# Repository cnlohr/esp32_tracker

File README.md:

# esp32_tracker
ESP32 Tracker with the TS4231

THIS PROJECT IS NOT YET FUNCTIONAL.

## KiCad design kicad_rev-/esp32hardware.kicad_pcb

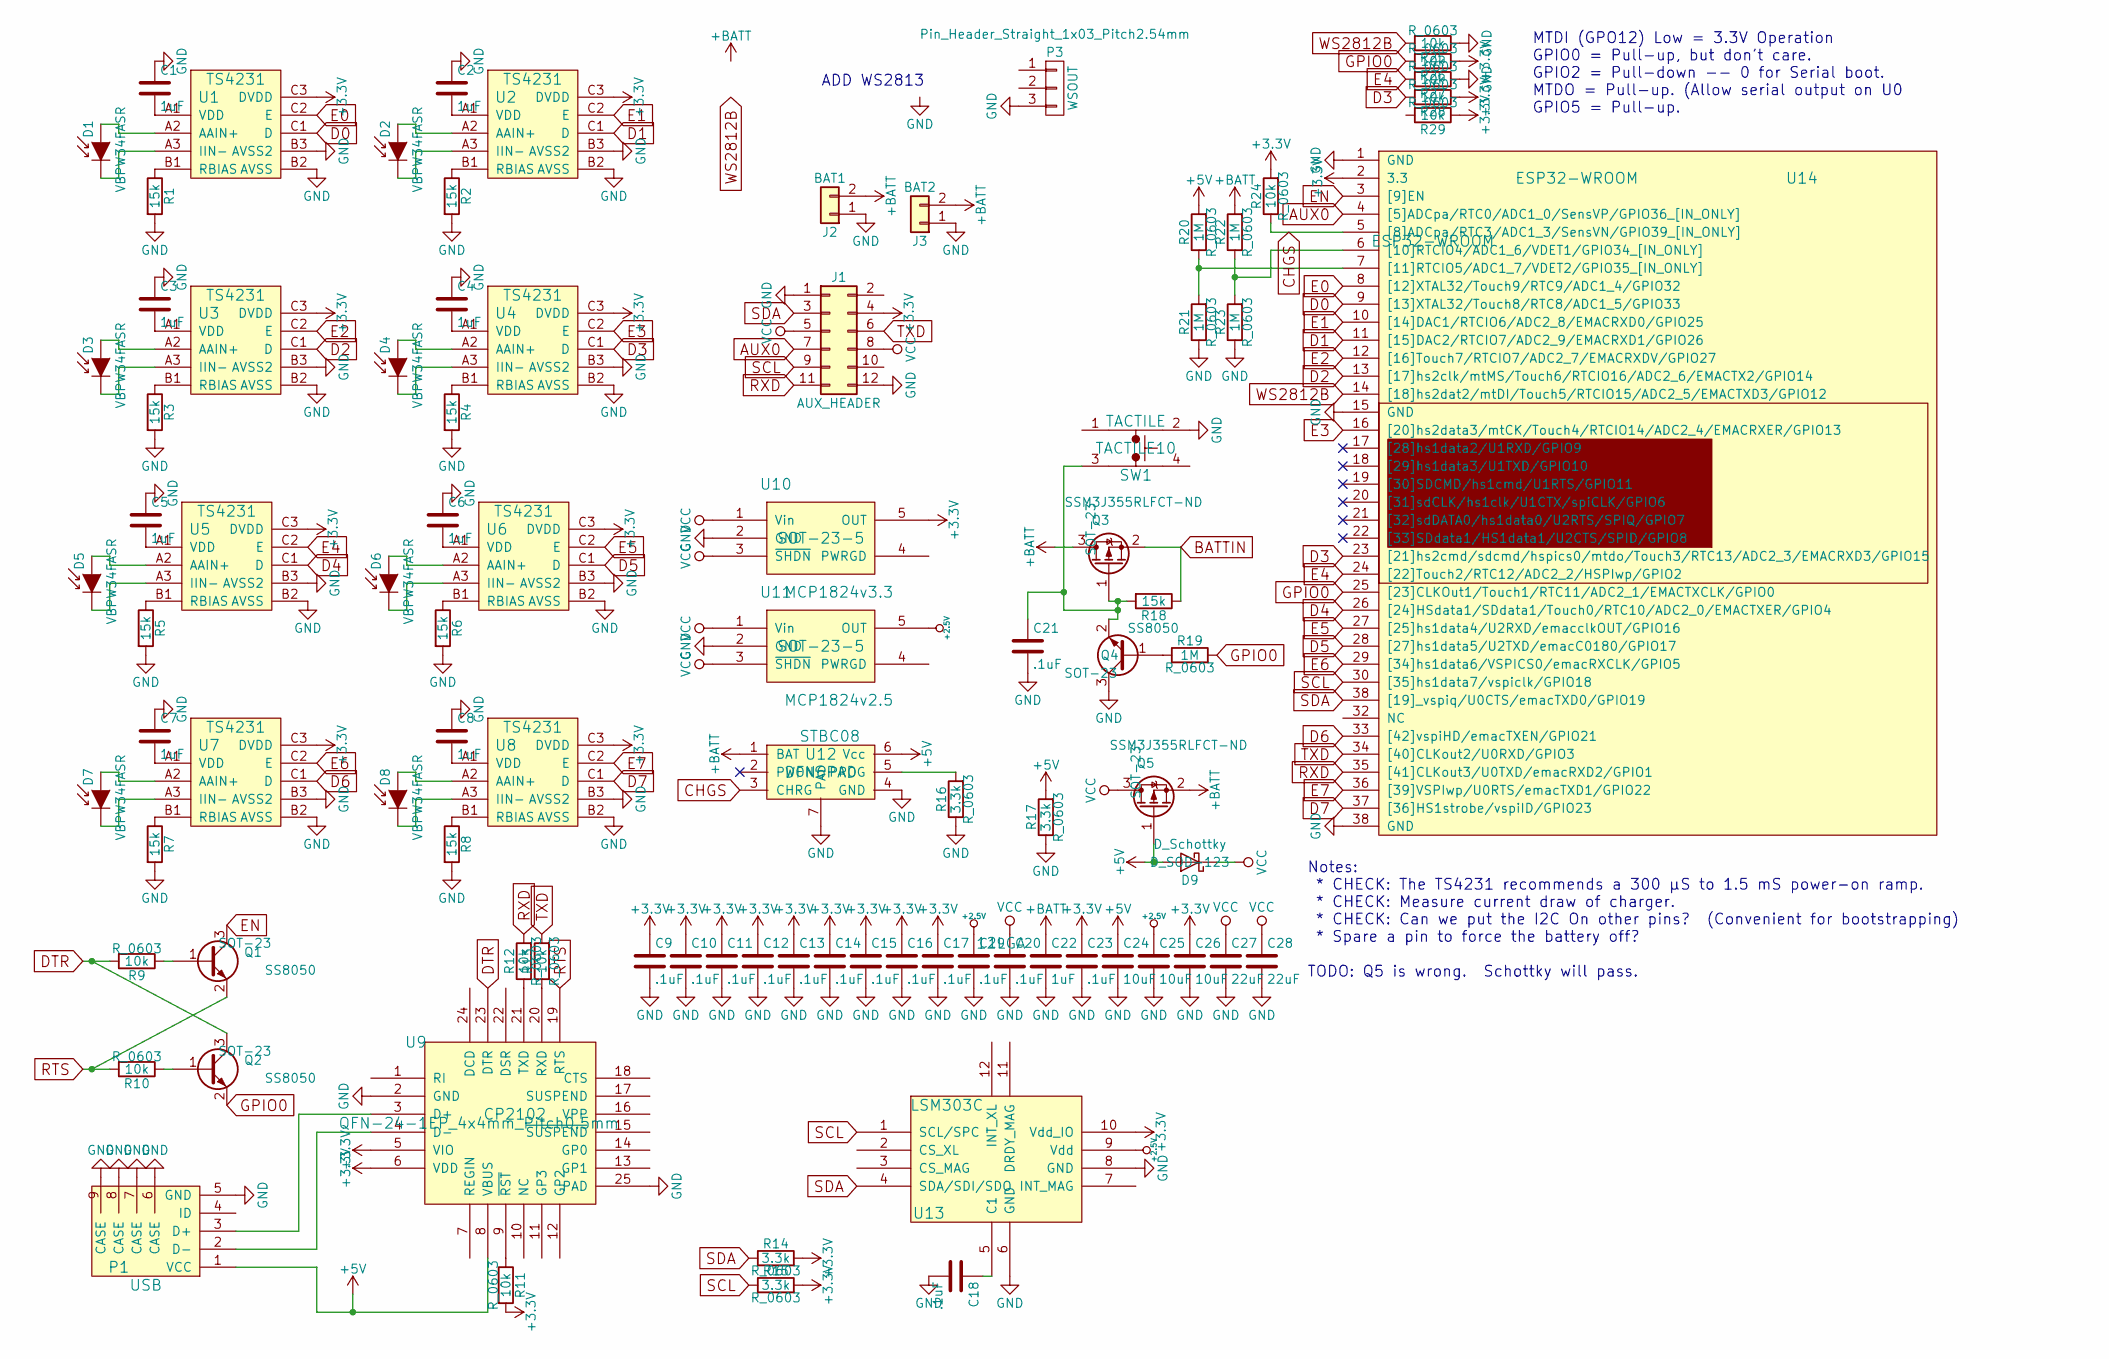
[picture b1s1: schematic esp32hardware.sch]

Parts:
C1, C2, C3, C4, C5, C6, C7, C8, C22: 1uF; C_0603
C9, C10, C11, C12, C13, C14, C15, C16, C17, C18, C19, C20, C21, C23: .1uF; C_0603
C24, C25, C26: 10uF; C_0603
C27, C28: 22uF; C_0603
D1, D2, D3, D4, D5, D6, D7, D8: VBPW34FASR
D9: D_Schottky; D_SOD-123
J1: AUX_HEADER; RIBBON12SMT
J2: BAT1; Pin_Header_Straight_1x02_Pitch2.54mm
J3: BAT2; Pin_Header_Straight_1x02_Pitch2.54mm
P1: USB; USBMicroB-10118194-0001LF
P3: WSOUT; Pin_Header_Straight_1x03_Pitch2.54mm
Q1, Q2, Q4: SS8050; SOT-23
Q3, Q5: SSM3J355RLFCT-ND; SOT-23
R1, R2, R3, R4, R5, R6, R7, R8, R18: 15k; R_0603
R9, R10, R11, R12, R13, R24, R25, R26, R27, R28, R29: 10k; R_0603
R14, R15, R16, R17: 3.3k; R_0603
R19, R20, R21, R22, R23: 1M; R_0603
SW1: TACTILE; TACTILE10
U1, U2, U3, U4, U5, U6, U7, U8: TS4231
U9: CP2102; QFN-24-1EP_4x4mm_Pitch0.5mm
U10: MCP1824v3.3; SOT-23-5
U11: MCP1824v2.5; SOT-23-5
U12: STBC08; DFN6PAD
U13: LSM303C; 12LGA
U14: ESP32-WROOM

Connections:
+2.5V: C19.1, C25.1, U11.5 (OUT), U13.9 (Vdd)
+3V3: C9.1, C10.1, C11.1, C12.1, C13.1, C14.1, C15.1, C16.1, C17.1, C23.1, C26.1, J1.4, R11.2, R14.2, R15.2, R24.2, R26.1, R28.1, R29.1, U1.C3 (DVDD), U2.C3 (DVDD), U3.C3 (DVDD), U4.C3 (DVDD), U5.C3 (DVDD), U6.C3 (DVDD), U7.C3 (DVDD), U8.C3 (DVDD), U9.5 (VIO), U9.6 (VDD), U10.5 (OUT), U13.10 (Vdd_IO), U14.2 (3.3)
+5V: C24.1, D9.2 (A), P1.1 (VCC), Q5.1 (G), R17.2, R20.2, U9.8 (VBUS), U12.6 (Vcc)
+BATT: C22.1, J2.2, J3.2, Q3.3 (D), Q5.2 (S), R22.2, U12.1 (BAT)
AUX0: J1.7, U14.4 ([5]ADCpa/RTC0/ADC1_0/SensVP/GPIO36_[IN_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)
BATTIN: Q3.2 (S), R18.1
CHGS: R24.1, U12.3 (CHRG), U14.5 ([8]ADCpa/RTC3/ADC1_3/SensVN/GPIO39_[IN_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)
D0: U1.C1 (D), U14.9 ([13]XTAL32/Touch8/RTC8/ADC1_5/GPIO33)
D1: U2.C1 (D), U14.11 ([15]DAC2/RTCIO7/ADC2_9/EMACRXD1/GPIO26)
D2: U3.C1 (D), U14.13 ([17]hs2clk/mtMS/Touch6/RTCIO16/ADC2_6/E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)
D3: R28.2, U4.C1 (D), U14.23 ([21]hs2cmd/sdcmd/hspics0/mtdo/Touch3/RT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)
D4: U5.C1 (D), U14.26 ([24]HSdata1/SDdata1/Touch0/RTC10/ADC2_0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)
D5: U6.C1 (D), U14.28 ([27]hs1data5/U2TXD/emacC0180/GPIO17)
D6: U7.C1 (D), U14.33 ([42]vspiHD/emacTXEN/GPIO21)
D7: U8.C1 (D), U14.37 ([36]HS1strobe/vspiID/GPIO23)
DTR: Q2.3 (C), R9.2, U9.23 (DTR)
E0: U1.C2 (E), U14.8 ([12]XTAL32/Touch9/RTC9/ADC1_4/GPIO32)
E1: U2.C2 (E), U14.10 ([14]DAC1/RTCIO6/ADC2_8/EMACRXD0/GPIO25)
E2: U3.C2 (E), U14.12 ([16]Touch7/RTCIO7/ADC2_7/EMACRXDV/GPIO27)
E3: U4.C2 (E), U14.16 ([20]hs2data3/mtCK/Touch4/RTCIO14/ADC2_4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)
E4: R27.2, U5.C2 (E), U14.24 ([22]Touch2/RTC12/ADC2_2/HSPIwp/GPIO2)
E5: U6.C2 (E), U14.27 ([25]hs1data4/U2RXD/emacclkOUT/GPIO16)
E6: U7.C2 (E), U14.29 ([34]hs1data6/VSPICS0/emacRXCLK/GPIO5)
E7: U8.C2 (E), U14.36 ([39]VSPIwp/U0RTS/emacTXD1/GPIO22)
EN: Q1.3 (C), U14.3 ([9]EN)
GPIO0: Q2.2 (E), R19.2, R26.2, U14.25 ([23]CLKOut1/Touch1/RTC11/ADC2_1/EMACTXC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)
unnamed: C1.2, U1.A1 (VDD)
unnamed: C2.2, U2.A1 (VDD)
unnamed: C3.2, U3.A1 (VDD)
unnamed: C4.2, U4.A1 (VDD)
unnamed: C5.2, U5.A1 (VDD)
unnamed: C6.2, U6.A1 (VDD)
unnamed: C7.2, U7.A1 (VDD)
unnamed: C8.2, U8.A1 (VDD)
unnamed: C18.1, U13.5 (C1)
unnamed: C21.1, Q3.1 (G), Q4.2 (E), R18.2, SW1.3
unnamed: D1.1 (K), U1.A3 (IIN-)
unnamed: D1.2 (A), U1.A2 (AAIN+)
unnamed: D2.1 (K), U2.A3 (IIN-)
unnamed: D2.2 (A), U2.A2 (AAIN+)
unnamed: D3.1 (K), U3.A3 (IIN-)
unnamed: D3.2 (A), U3.A2 (AAIN+)
unnamed: D4.1 (K), U4.A3 (IIN-)
unnamed: D4.2 (A), U4.A2 (AAIN+)
unnamed: D5.1 (K), U5.A3 (IIN-)
unnamed: D5.2 (A), U5.A2 (AAIN+)
unnamed: D6.1 (K), U6.A3 (IIN-)
unnamed: D6.2 (A), U6.A2 (AAIN+)
unnamed: D7.1 (K), U7.A3 (IIN-)
unnamed: D7.2 (A), U7.A2 (AAIN+)
unnamed: D8.1 (K), U8.A3 (IIN-)
unnamed: D8.2 (A), U8.A2 (AAIN+)
unnamed: P1.2 (D-), U9.4 (D-)
unnamed: P1.3 (D+), U9.3 (D+)
unnamed: Q1.1 (B), R9.1
unnamed: Q2.1 (B), R10.1
unnamed: Q4.1 (B), R19.1
unnamed: R1.1, U1.B1 (RBIAS)
unnamed: R2.1, U2.B1 (RBIAS)
unnamed: R3.1, U3.B1 (RBIAS)
unnamed: R4.1, U4.B1 (RBIAS)
unnamed: R5.1, U5.B1 (RBIAS)
unnamed: R6.1, U6.B1 (RBIAS)
unnamed: R7.1, U7.B1 (RBIAS)
unnamed: R8.1, U8.B1 (RBIAS)
unnamed: R11.1, U9.9 (~RST~)
unnamed: R12.1, U9.21 (TXD)
unnamed: R13.1, U9.20 (RXD)
unnamed: R16.2, U12.5 (PROG)
unnamed: R20.1, R21.2, U14.7 ([11]RTCIO5/ADC1_7/VDET2/GPIO35_[IN_ONLY])
unnamed: R22.1, R23.2, U14.6 ([10]RTCIO4/ADC1_6/VDET1/GPIO34_[IN_ONLY])
RTS: Q1.2 (E), R10.2, U9.19 (RTS)
RXD: J1.11, R12.2, U14.35 ([41]CLKout3/U0TXD/emacRXD2/GPIO1)
SCL: J1.9, R15.1, U13.1 (SCL/SPC), U14.30 ([35]hs1data7/vspiclk/GPIO18)
TXD: J1.6, R13.2, U14.34 ([40]CLKout2/U0RXD/GPIO3)
VCC: C20.1, C27.1, C28.1, D9.1 (K), J1.5, J1.8, Q5.3 (D), U10.1 (Vin), U10.3 (~SHDN), U11.1 (Vin), U11.3 (~SHDN)
WS2812B: R25.2, U14.14 ([18]hs2dat2/mtDI/Touch5/RTCIO15/ADC2_5/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)

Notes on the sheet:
MTDI (GPO12) Low = 3.3V Operation GPIO0 = Pull-up, but don't care. GPIO2 = Pull-down -- 0 for Serial boot. MTDO = Pull-up. (Allow serial output on U0 GPIO5 = Pull-up.
Notes: * CHECK: The TS4231 recommends a 300 μS to 1.5 mS power-on ramp. * CHECK: Measure current draw of charger. * CHECK: Can we put the I2C On other pins? (Convenient for bootstrapping) * Spare a pin to force the battery off? TODO: Q5 is wrong. Schottky will pass.
ADD WS2813

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
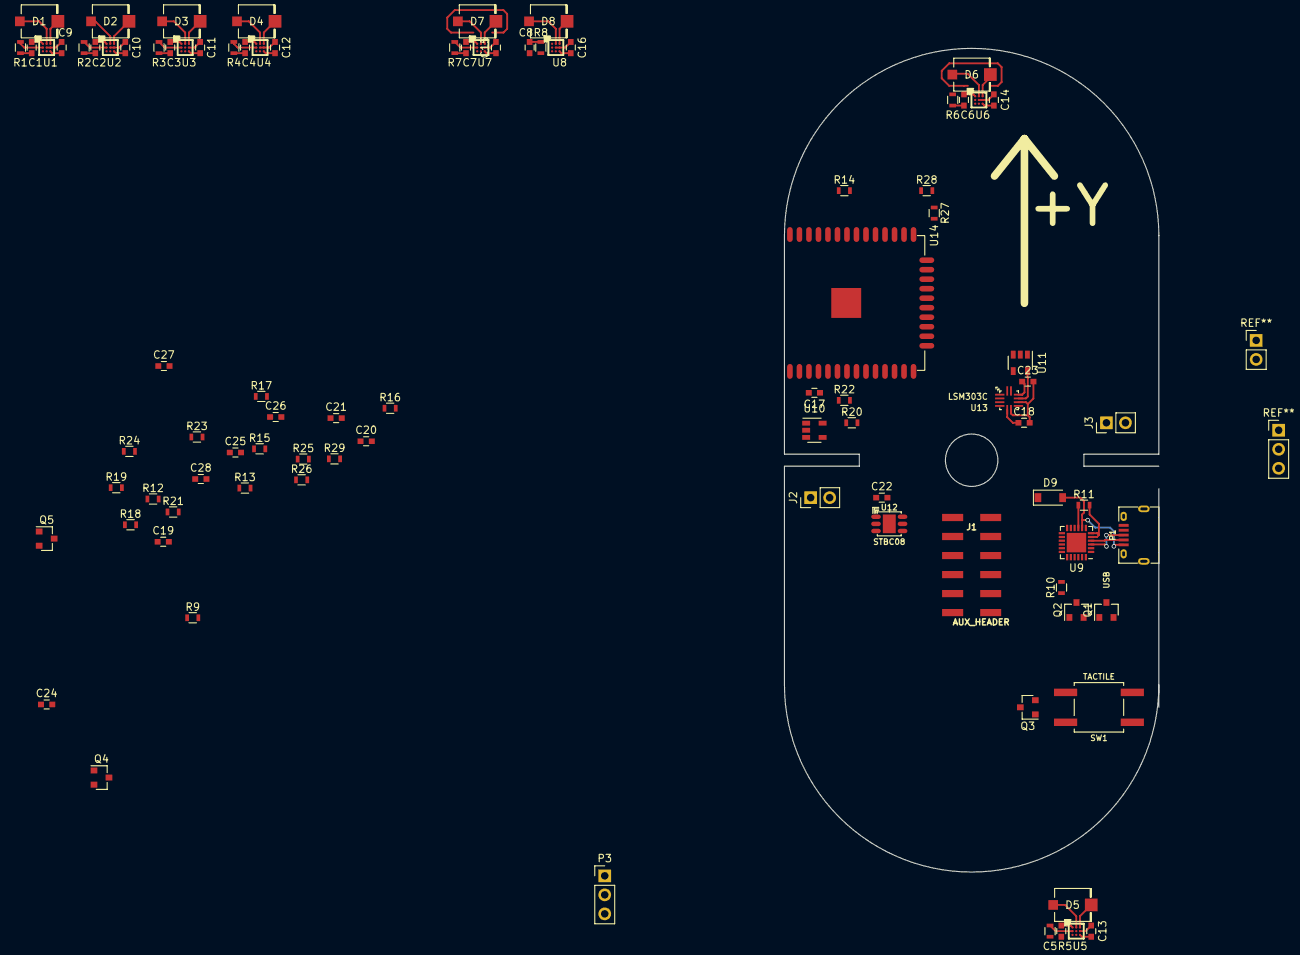
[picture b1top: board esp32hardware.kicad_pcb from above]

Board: 2 copper layers, 50.0 x 110.0 mm, 91 parts (0 on the bottom side), 79 nets.

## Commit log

2018-03-27 ADd kiard hardware
2018-03-28 More progress...
